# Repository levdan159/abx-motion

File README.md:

# ABX-Motion Rev 1.2b — Ethernet routing draft

Open [abx-motion.kicad_pro](abx-motion.kicad_pro) in the project root. The root PCB and schematic hierarchy now contain the reviewed Ethernet development checkpoint, promoted from [ABX-Motion-ETH](variants/ABX-Motion-ETH/README.txt). Assembly option: **ABX-MOTION-ETH**. No PoE.

Current [DRC cleanup verification](validation/drc-cleanup-20261024/README.txt): **0 DRC violations, 0 defined-net opens, 0 schematic-parity issues and 0 ERC violations**. No rules were relaxed or findings excluded. The 49 unwired Ethernet placement reserves are explicitly board-only and still excluded from BOM/CPL. A clean DRC does not make those reserves functional.

The dedicated Ethernet 3.3 V converter is schematic-integrated and routed, and connections displaced by Ethernet placement are restored. The W5500, RJ45, clock, protection, reset and SPI interface still have **49 unintegrated draft footprints**. This is **not a manufacturing release**. Zero opens on defined nets does not establish complete Ethernet connectivity.

The checkpoint retains the three onboard DRV8462 drivers, external stepper interfaces, eight-socket digital I/O bank, axis legends and thermal copper/TIM windows. The PCB is four layers; In1.Cu remains the ground plane. The audited project minimum clearance and track width are both 0.15 mm.

See [root promotion QA](validation/root-ethernet-promotion-20261024/README.txt), [Ethernet routing preview](variants/ABX-Motion-ETH/layout-review/routing-overview.png), and [remaining circuit requirements](variants/ABX-Motion-ETH/layout-review/power-routing-plan.txt). The earlier Rev1.2a CAD is recoverable from Git commit `ce34a43`; its [JLCPCB prototype package](production/rev-1.2a-20261023/README.txt) is preserved and **does not describe this Rev1.2b draft**. Earlier exports and renders remain historical. Do not run legacy rebuild/router scripts over the active root project.

The original local project settings were saved before promotion in `work/root-ethernet-promotion-20261024/before/`. Root schematic instance project names and library paths were adapted for `abx-motion`; the reviewed PCB was promoted, then obsolete copper, thermal-aperture routing and silkscreen were cleaned up with connectivity checks. Ethernet 3D models are bundled under `abx-3dmodels/ethernet/`; see the [model-loading verification](validation/root-model-fix-20261024/README.txt).

## Historical Rev 1.1 documentation

The content below describes the preserved Rev 1.1 prototype and its exports. StepStick socket details, firmware allocations, component counts and images below do not describe the active Rev 1.2b draft. The preserved Rev 1.1d manufacturing package is `production/rev-1.1d-20261020/`. Do not run legacy rebuild/router scripts over the active root placement.

# ABX-Motion Rev 1.1c prototype controller

Compact **157 × 105 mm, four-layer** ESP32-S3 motion controller. This layout is
intended for controlled prototype testing. Printed voltage, motor-power and
fuse ratings are design targets, not measured board ratings.

## Hardware

- ESP32-S3-WROOM-1-N8R2, native USB-C programming, RESET/BOOT buttons,
  CAN, RS-485, I²C OLED header and BACK/OK/FWD controls.
- Two DRV8701E brushed-motor bridges with encoder inputs, 10 mΩ shunts
  and configurable gate-drive resistors.
- Two StepStick sockets and external STEP/DIR/EN connectors. Check each
  carrier's pinout, enable polarity, voltage range and mode straps before use.
- Two SPDT relays. Contact ratings do not establish PCB current capability.
- XT60 input, Keystone 3557-2 fuse holder, reverse-polarity P-MOSFET,
  TVS3300 precision pulse clamp, 5 V buck and 3.3 V LDO.
- Front and rear exposed-copper gears (`F.Cu`/`F.Mask` and `B.Cu`/`B.Mask`)
  with white silkscreen text (`AUTOBOTIX` / `ABX-Motion Rev 1.1c`). Select ENIG for
  gold artwork.

## Compact I/O

J601–J606 use identical three-pin JST-PH headers. Read the per-pin markings:
output headers have a different function from limit headers.

| Headers | Channel | Pin 1 | Pin 2 | Pin 3 |
| --- | --- | --- | --- | --- |
| J601 | DC motor 1 limits | MIN | GND | MAX |
| J602 | DC motor 2 limits | MIN | GND | MAX |
| J603 | Stepper 1 limits | MIN | GND | MAX |
| J604 | Stepper 2 limits | MIN | GND | MAX |
| J605 | Auxiliary output 1 | +5V_OUT | GND | SW1 |
| J606 | Auxiliary output 2 | +5V_OUT | GND | SW2 |

The eight limit channels have 3.3 V pull-ups, series resistors and RC filtering.
Use dry contacts to ground or compatible 3.3 V logic. **Do not connect 12/24 V
sensors directly.** Normally closed contacts let firmware treat a broken wire
as an active limit. Configured as outputs, these are resistor-limited logic
signals, not load drivers.

Connect a 5 V auxiliary load between +5V_OUT and SW1/SW2. SW pins are low-side
MOSFET drains. Both headers share F5: **Littelfuse 1206L050/15YR, C151162**,
500 mA hold at 20 °C, 15 V. The PTC is not a precise 500 mA current limiter;
temperature, trip delay and the total 5 V supply budget constrain usable loads.

## Firmware and stopping

PCA9555 U601 is at I²C address 0x20 on GPIO41 (SDA) / GPIO42 (SCL).
Its active-low interrupt uses GPIO36; BACK uses GPIO21.
Port 0 bits 0–7 are limits in the table's MIN/MAX order.
Port 1 bits 0/1 command auxiliary outputs, bits 2/3 command active-low
stepper enables, and bit 4 reads E-stop status. Bits 5–7 are grounded and
must remain inputs.

On startup, keep both ports as inputs, write Port 1 output latch **0x0C**
(outputs off, steppers disabled), then configure Port 1 with **0xF0**. Keep
Port 0 configuration **0xFF** for limit sensing. Read inputs to acknowledge
interrupts. An ESP32 reset does not reset the independently powered expander;
reinitialize it on every boot and test reboot behavior under load. No application
firmware is supplied in this repository yet.

The hardware E-stop net disables DC bridges and gates onboard/external
stepper enables. Relays and auxiliary outputs remain powered. Verify stop
behavior with each actual attached driver. Firmware must block travel into an
active limit while allowing controlled retreat; I²C limit sensing is not an
independent hardware overtravel interlock.

## Validation and first power-up

**Prototype status:** CAD checks pass for the saved prototype candidate.
Powered motor, thermal and fault qualification requires the first boards;
it is not a prerequisite for fabricating them. Confirm relay alignment with
the assembler before assembly: the supplier CAD conflicts with Omron's hole
drawing. Full-power operation and the return-energy/protection envelope
remain unqualified. The small D2 TVS is not a braking-energy sink, and
parallel TVS parts do not guarantee current sharing. See
`validation/robustness-final-20261020/review.txt` and the matched files in
`production/rev-1.1d-20261020/`. Supplier numbered-pad checks verify D2,
U601 and all six PH connector directions.

The supply target is conventional 7S lithium ion (29.4 V fully charged), with
a 32 V normal ceiling. First power at the intended voltage needs controlled
fault energy/current, motors disconnected and drivers disabled. A 12 V test
is not required. Check rails, USB programming, expander defaults, all eight
inputs, auxiliary outputs and E-stop before adding one unloaded motor at low
current. Measure switching transients, rail ripple, current accuracy and
temperatures before increasing load. D2 is now TI TVS3300DRVR (C2863624):
33 V standoff, 40 V maximum clamp under TI's specified 8/20 us surge conditions.
The SON package rating is 35 A at 8/20 us but only 3.5 A at 10/1000 us. It is
not a continuous braking load. Regenerative loads require a battery/BMS that
accepts their charging current or a separately sized braking clamp. Do not
substitute a TMC2209 carrier for 7S/32 V use; its operating maximum is 29 V.
Q1 heating, LDO dissipation and motor-capacitor ripple capability also need
measurement. Confirm the OLED module's physical hole/header dimensions before
ordering (`H5`/`H6` M2 holes are at `23.30 mm` actual X spacing vs `23.0 mm`
nominal silkscreen callout, `23.80 mm` below `J208`); SSD1306 module names do
not guarantee a common hole pattern.

Assembly BOM correction (20 October 2026): StepStick sockets use four C27438
1x8 female strips, with 1.0 mm PCB holes per the supplier drawing. The earlier
C145755 entry was a temperature sensor and must not be assembled. The current
BOM has 66 supplier/footprint groups for 239 placements; repeated connector,
LED and switch selections are consolidated. Upload the matching new Gerbers,
BOM and CPL together. F1 is a holder; obtain the actual blade fuse separately.

Robustness revision (20 October 2026): R2=150k above R3=10k gives a nominal
**VBAT/16** ADC input. R313/R413=1k form 1:2 dividers with R304/R404; the MCU
now measures **SO/2**. Firmware must calculate shunt current using
`I = (2*Vadc - calibrated_SO_offset) / (20*0.010)` with actual gain/offset
calibration. Rev 1.1c separately lowers the chopping threshold through
R302/R402; the ADC divider does not set that threshold. R6=22k reduces battery
LED heating. All pre-existing signal routing and component positions except
D2's local footprint remain preserved. No application firmware is supplied.
Use the saved native design and the matching package. Legacy stage/router
scripts restore older checkpoints and must not be used to export this revision.

## Hardware revision

The current hardware identifier is **ABX-Motion Rev 1.1d**. `Rev` identifies
the PCB hardware; firmware versions are separate. Rev 1.1b included the
ADC input dividers, battery-divider/LED resistor updates, corrected socket
selection and assembly audit. Relay alignment needs assembler confirmation;
powered qualification follows prototype receipt. Revision lettering does
not imply qualified operating ratings. Rev 1.1c additionally changes R302/R402 from 30k to 12k (C22790) to lower
the DC current-chopping target from 14.75 A to 9.35 A nominal. The analytical
static corner estimate is about 6.7–11.8 A, before temperature drift, ground-layout errors and blanking/propagation
overshoot; it is not a guaranteed current bound. Layout and copper routing are unchanged. This may restrict torque
for low-voltage motors operated through PWM; it is not a 150 W power limiter.

## Motor robustness and bench acceptance

Design case: two DC motors, each drawing up to 150 W electrically for one
second; 300 W combined excludes StepStick loads and other peripherals. This
is a proposed intermittent operating envelope, not a measured board rating.
Motor winding current can exceed battery current under PWM. Current chopping
does not protect arbitrary low-inductance motors, brake-mode currents or a
sustained short. DRV8701 retries faults automatically; its die-temperature
shutdown does not measure the external MOSFETs or Q1.

Follow `validation/robustness-final-20261020/bench-procedure.txt` at the intended
pack voltage with fault energy limited before connecting motors. No physical
load, thermal, stall or regenerative test has yet been performed. Do not infer
safety from the 25 A holder label or 150 W motor power. Use actual phase-current
measurements, a timed stop and a verified return-energy path during testing.

## Thermal layout revision — Rev 1.1d

Local net-specific thermal vias and backside copper spread heat from Q1
and the motor bridge MOSFETs. A grounded top copper spreader connects the
ESP32 module centre pad to its surroundings, retaining its twelve existing
plated thermal holes and antenna keepout. U2 gains a small grounded spreader;
its SOT-23 package still limits continuous dissipation. Existing buck and
gate-driver thermal arrays remain unchanged. No component positions, lead
pads, original routing, electrical values or connector orientations change.
See `validation/thermal-20261020/review.txt` for checked scope and limitations.
MOSFET drain copper is electrically live; a common metal heatsink requires
an electrically insulating thermal interface. Added vias are outside solder
lands and tented on both faces. This is a heat-path improvement, not a
measured temperature or continuous-current qualification.

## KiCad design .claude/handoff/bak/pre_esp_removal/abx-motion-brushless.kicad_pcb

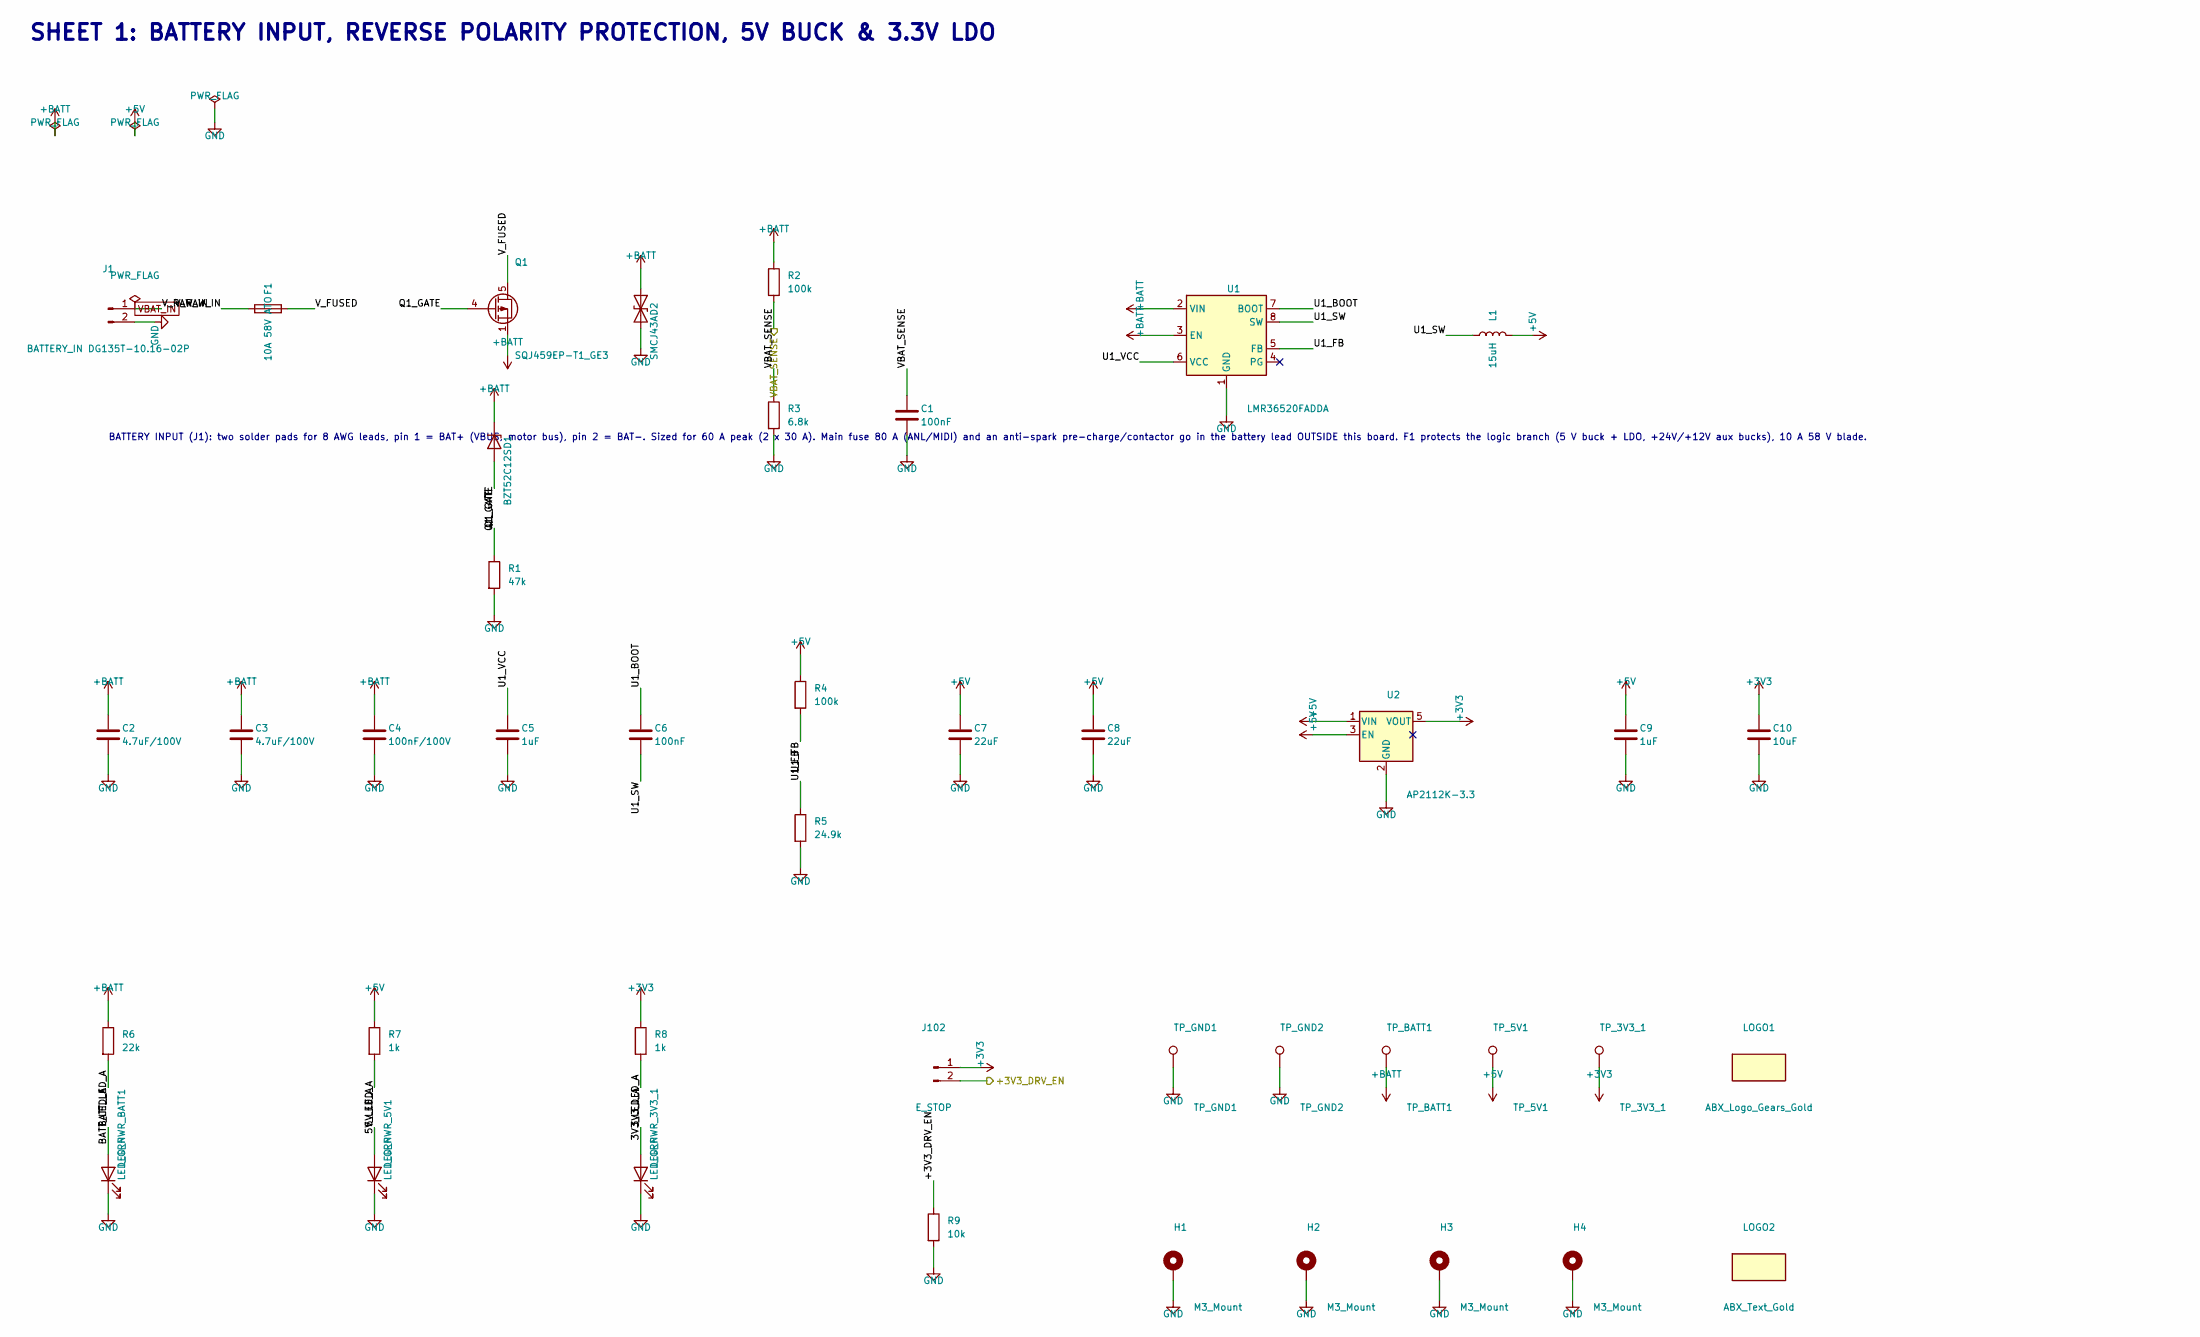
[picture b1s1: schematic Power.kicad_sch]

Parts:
C1, C6: 100nF; C_0603_1608Metric
C2, C3: 4.7uF/100V; C_1206_3216Metric
C4: 100nF/100V; C_0603_1608Metric
C5, C9: 1uF; C_0603_1608Metric
C7, C8: 22uF; C_1206_3216Metric
C10: 10uF; C_0805_2012Metric
D1: BZT52C12S; D_SOD-323
D2: SMCJ43A; D_SMC
F1: 10A 58V ATO; Fuseholder_Keystone_3557-2
H1, H2, H3, H4: M3_Mount; MountingHole_3.2mm_M3_Pad_Via
J1: BATTERY_IN DG135T-10.16-02P; ABX_Degson_DG135T-10.16-02P
J102: E_STOP; TerminalBlock_Phoenix_MKDS-1,5-2-5.08_1x02_P5.08mm_Horizont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
L1: 15uH; L_Bourns_SRP7028A_7.3x6.6mm
LED_PWR_3V3_1, LED_PWR_5V1: LED_GRN; LED_0603_1608Metric
LED_PWR_BATT1: LED_GRN; LED_0603_1608Metric
LOGO1: ABX_Logo_Gears_Gold
LOGO2: ABX_Text_Gold
Q1: SQJ459EP-T1_GE3; TDSON-8-1
R1: 47k; R_0603_1608Metric
R2, R4: 100k; R_0603_1608Metric
R3: 6.8k; R_0603_1608Metric
R5: 24.9k; R_0603_1608Metric
R6: 22k; R_0603_1608Metric
R7, R8: 1k; R_0603_1608Metric
R9: 10k; R_0603_1608Metric
TP_3V3_1: TP_3V3_1; TestPoint_Pad_D1.5mm
TP_5V1: TP_5V1; TestPoint_Pad_D1.5mm
TP_BATT1: TP_BATT1; TestPoint_Pad_D1.5mm
TP_GND1: TP_GND1; TestPoint_Pad_D1.5mm
TP_GND2: TP_GND2; TestPoint_Pad_D1.5mm
U1: LMR36520FADDA; Texas_HSOP-8-1EP_3.9x4.9mm_P1.27mm_ThermalVias
U2: AP2112K-3.3; SOT-23-5

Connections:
+3V3: C10.1, J102.1, R8.1, TP_3V3_1.1 (1_1), U2.5 (VOUT); also elsewhere on the board
+5V: C7.1, C8.1, C9.1, L1.2, R4.1, R7.1, TP_5V1.1 (1_1), U2.1 (VIN), U2.3 (EN); also elsewhere on the board
+BATT: C2.1, C3.1, C4.1, D1.1 (K), D2.1 (A1), Q1.1 (S), Q1.2 (S), Q1.3 (S), R2.1, R6.1, TP_BATT1.1 (1_1), U1.2 (VIN), U1.3 (EN); also elsewhere on the board
/+3V3_DRV_EN: J102.2, R9.1; also elsewhere on the board
/Power_Supply/3V3_LED_A: LED_PWR_3V3_1.2 (A), R8.2
/Power_Supply/5V_LED_A: LED_PWR_5V1.2 (A), R7.2
/Power_Supply/BATT_LED_A: LED_PWR_BATT1.2 (A), R6.2
/Power_Supply/Q1_GATE: D1.2 (A), Q1.4 (G), R1.1
/Power_Supply/U1_BOOT: C6.1, U1.7 (BOOT)
/Power_Supply/U1_FB: R4.2, R5.1, U1.5 (FB)
/Power_Supply/U1_SW: C6.2, L1.1, U1.8 (SW)
/Power_Supply/U1_VCC: C5.1, U1.6 (VCC)
/Power_Supply/V_FUSED: F1.2, Q1.5 (D)
/VBAT_SENSE: C1.1, R2.2, R3.1; also elsewhere on the board
VBAT_IN: F1.1, J1.1; also elsewhere on the board

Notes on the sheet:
SHEET 1: BATTERY INPUT, REVERSE POLARITY PROTECTION, 5V BUCK & 3.3V LDO
BATTERY INPUT (J1): two solder pads for 8 AWG leads, pin 1 = BAT+ (VBUS, motor bus), pin 2 = BAT-. Sized for 60 A peak (2 x 30 A). Main fuse 80 A (ANL/MIDI) and an anti-spark pre-charge/contactor go in the battery lead OUTSIDE this board. F1 protects the logic branch (5 V buck + LDO, +24V/+12V aux 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

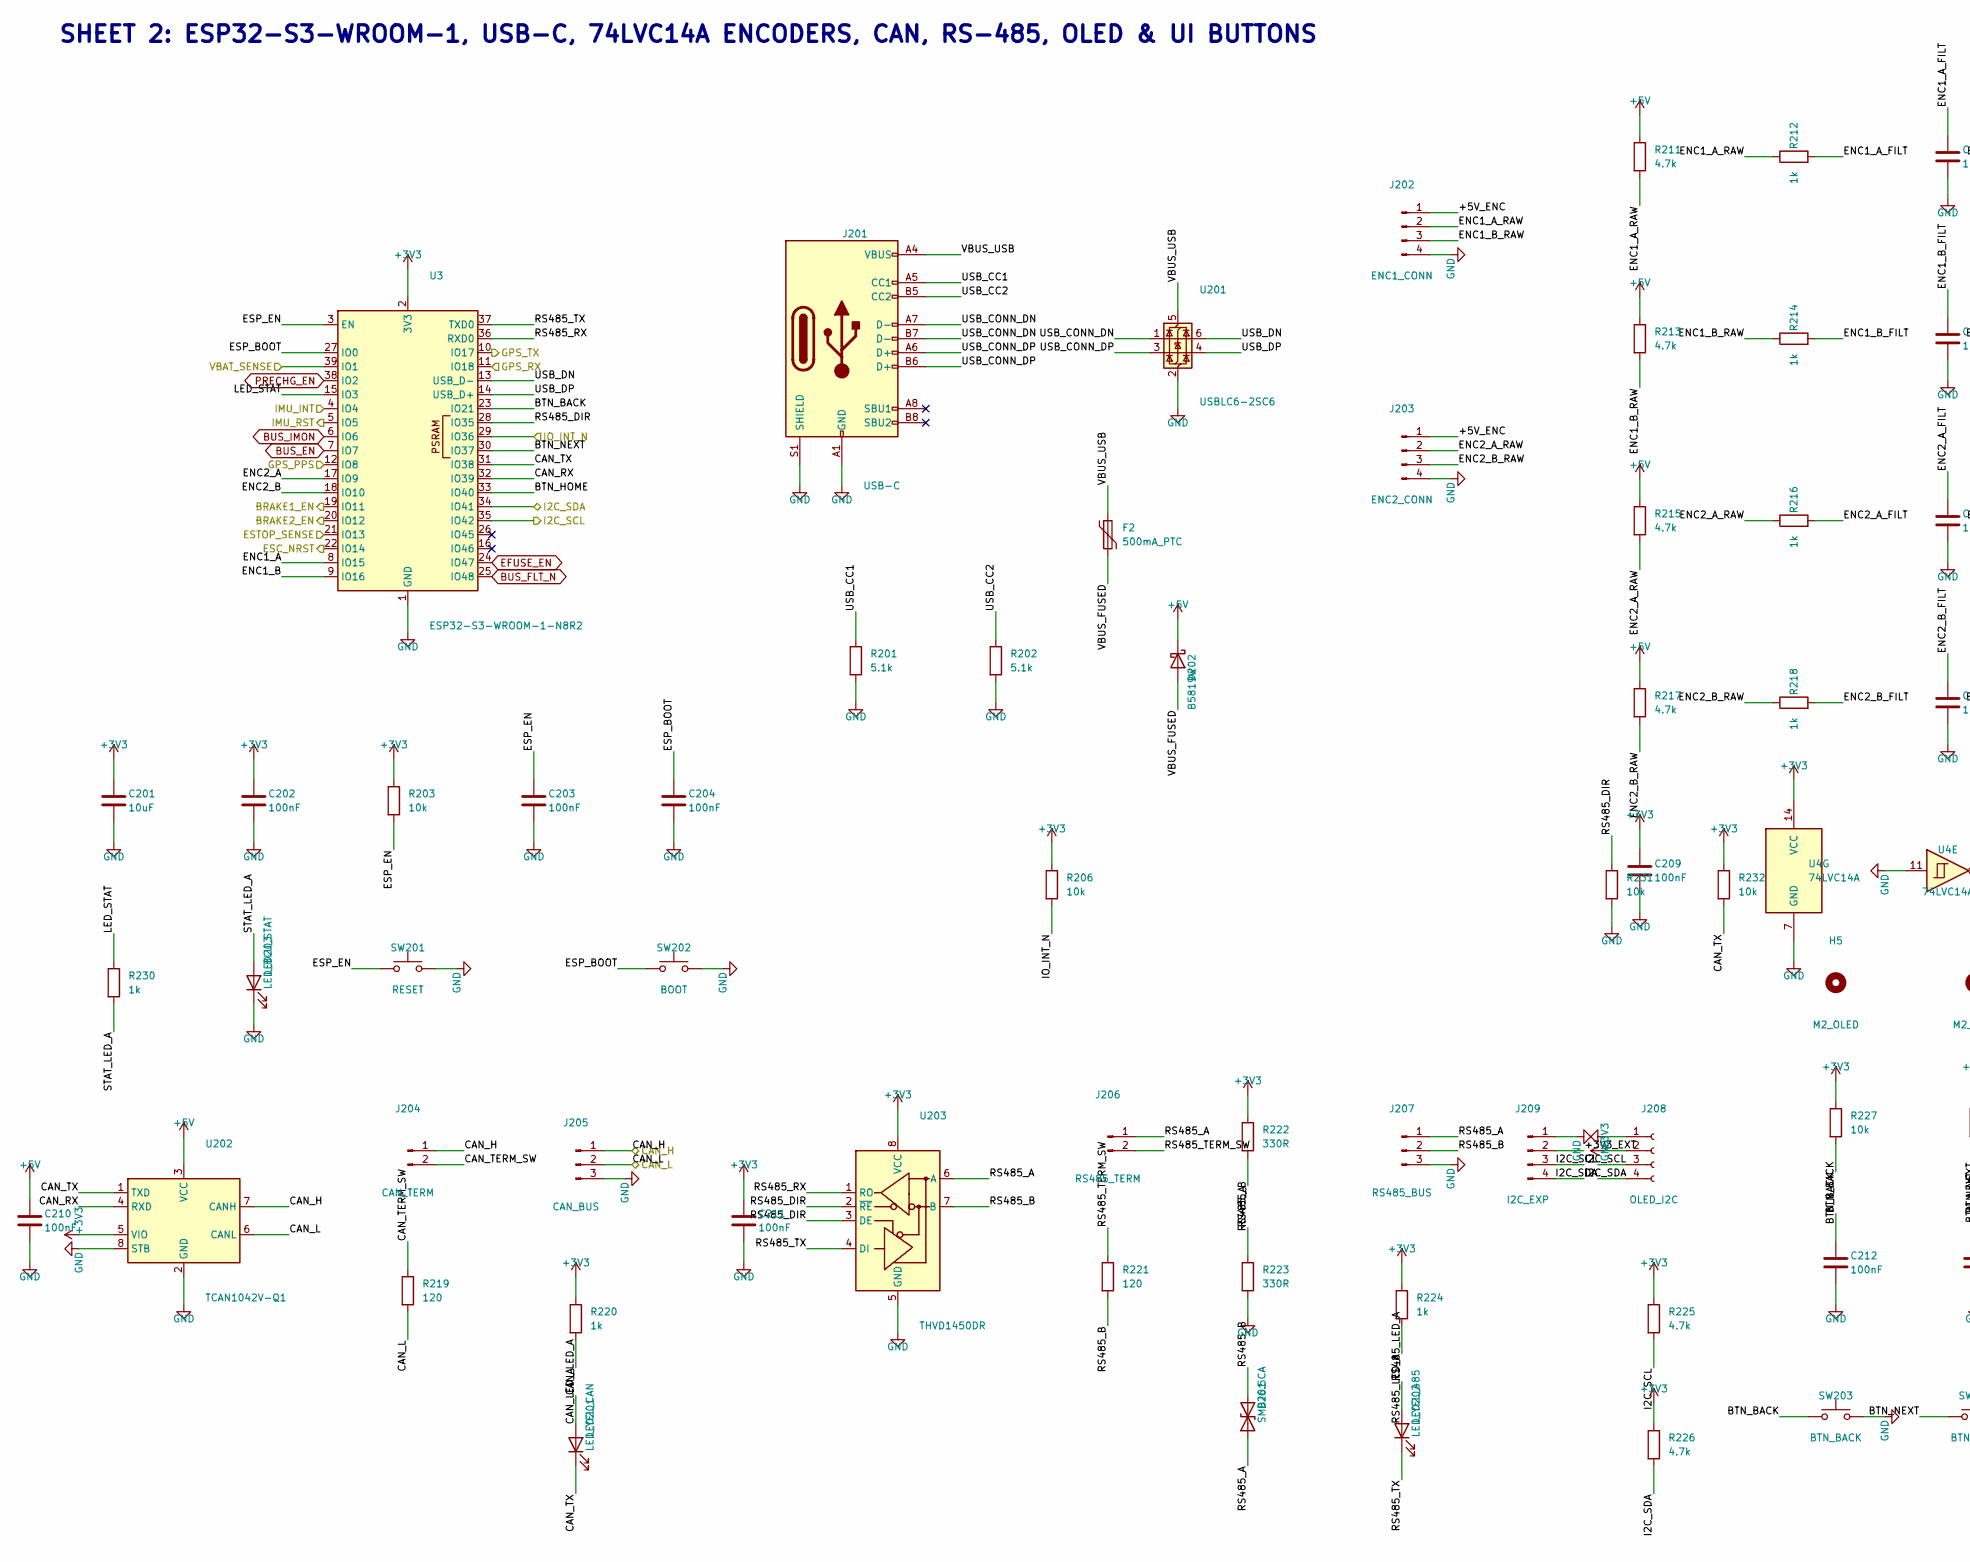
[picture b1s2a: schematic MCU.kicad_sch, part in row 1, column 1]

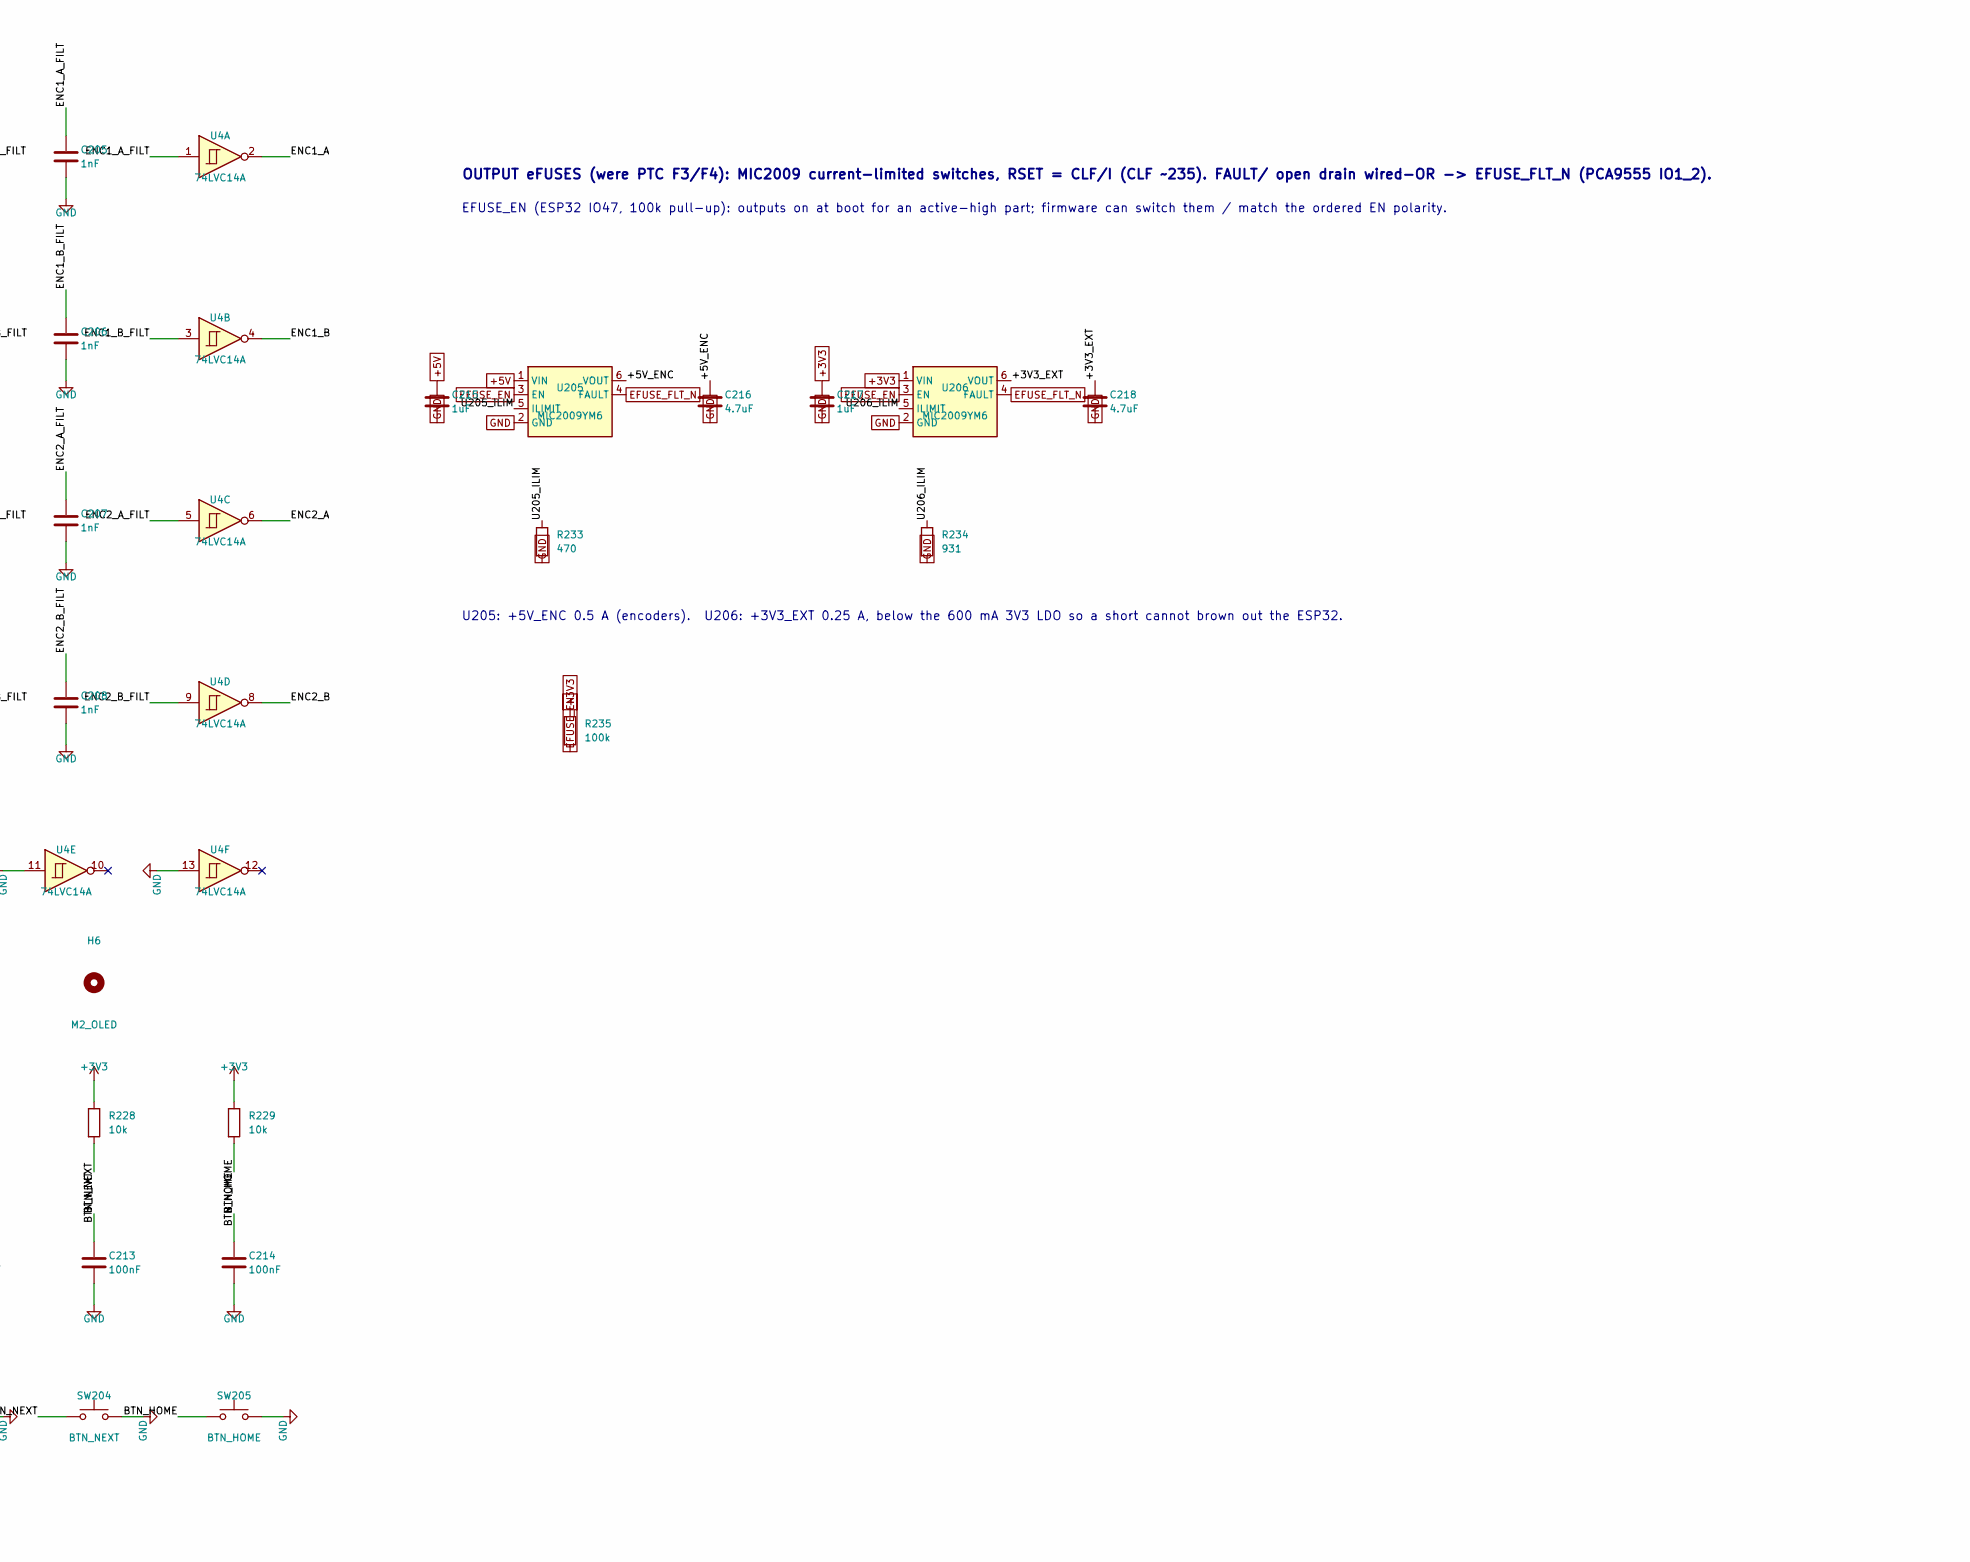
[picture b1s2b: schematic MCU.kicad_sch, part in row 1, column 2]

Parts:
C201: 10uF; C_0805_2012Metric
C202, C203, C204, C209, C210, C211, C212, C213, C214: 100nF; C_0603_1608Metric
C205, C206, C207, C208: 1nF; C_0603_1608Metric
C215, C217: 1uF; C_0603_1608Metric
C216, C218: 4.7uF; C_0805_2012Metric
D201: SMBJ6.5CA; D_SMB
D202: B5819W; D_SOD-123
F2: 500mA_PTC; Fuse_1206_3216Metric
H5, H6: M2_OLED; MountingHole_2.2mm_M2
J201: USB-C; USB_C_Receptacle_HRO_TYPE-C-31-M-12
J202: ENC1_CONN; JST_XH_B4B-XH-A_1x04_P2.50mm_Vertical
J203: ENC2_CONN; JST_XH_B4B-XH-A_1x04_P2.50mm_Vertical
J204: CAN_TERM; PinHeader_1x02_P2.54mm_Vertical
J205: CAN_BUS; TerminalBlock_Phoenix_MKDS-1,5-3-5.08_1x03_P5.08mm_Horizont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
J206: RS485_TERM; PinHeader_1x02_P2.54mm_Vertical
J207: RS485_BUS; TerminalBlock_Phoenix_MKDS-1,5-3-5.08_1x03_P5.08mm_Horizont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
J208: OLED_I2C; PinSocket_1x04_P2.54mm_Vertical
J209: I2C_EXP; JST_XH_B4B-XH-A_1x04_P2.50mm_Vertical
LED201: LED_YEL_CAN; LED_0603_1608Metric
LED202: LED_YEL_485; LED_0603_1608Metric
LED203: LED_BLU_STAT; LED_0603_1608Metric
R201, R202: 5.1k; R_0603_1608Metric
R203, R206, R227, R228, R229, R231, R232: 10k; R_0603_1608Metric
R211, R213, R215, R217, R225, R226: 4.7k; R_0603_1608Metric
R212, R214, R216, R218, R220, R224, R230: 1k; R_0603_1608Metric
R219, R221: 120; R_0603_1608Metric
R222, R223: 330R; R_0603_1608Metric
R233: 470; R_0603_1608Metric
R234: 931; R_0603_1608Metric
R235: 100k; R_0603_1608Metric
SW201: RESET; SW_SPST_B3U-1000P
SW202: BOOT; SW_SPST_B3U-1000P
SW203: BTN_BACK; SW_SPST_B3U-1000P
SW204: BTN_NEXT; SW_SPST_B3U-1000P
SW205: BTN_HOME; SW_SPST_B3U-1000P
U3: ESP32-S3-WROOM-1-N8R2; ESP32-S3-WROOM-1
U4: 74LVC14A; SOIC-14_3.9x8.7mm_P1.27mm
U201: USBLC6-2SC6; SOT-23-6
U202: TCAN1042V-Q1; SOIC-8_3.9x4.9mm_P1.27mm
U203: THVD1450DR; SOIC-8_3.9x4.9mm_P1.27mm
U205, U206: MIC2009YM6; SOT-23-6

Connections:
+3V3: C201.1, C202.1, C209.1, C211.1, C217.1, J208.2, R203.1, R206.1, R220.1, R222.1, R224.1, R225.1, R226.1, R227.1, R228.1, R229.1, R232.1, R235.1, U3.2 (3V3), U4.14 (VCC), U202.5 (VIO), U203.8 (VCC), U206.1 (VIN); also elsewhere on the board
+5V: C210.1, C215.1, D202.1 (K), R211.1, R213.1, R215.1, R217.1, U202.3 (VCC), U205.1 (VIN); also elsewhere on the board
/BRAKE1_EN: U3.19 (IO11); also elsewhere on the board
/BRAKE2_EN: U3.20 (IO12); also elsewhere on the board
/CAN_H: J204.1, J205.1, U202.7 (CANH); also elsewhere on the board
/CAN_L: J205.2, R219.2, U202.6 (CANL); also elsewhere on the board
/ESC_NRST: U3.22 (IO14); also elsewhere on the board
/ESTOP_SENSE: U3.21 (IO13); also elsewhere on the board
/GPS_PPS: U3.12 (IO8); also elsewhere on the board
/GPS_RX: U3.11 (IO18); also elsewhere on the board
/GPS_TX: U3.10 (IO17); also elsewhere on the board
/I2C_SCL: J208.3, J209.3, R225.2, U3.35 (IO42); also elsewhere on the board
/I2C_SDA: J208.4, J209.4, R226.2, U3.34 (IO41); also elsewhere on the board
/IMU_INT: U3.4 (IO4); also elsewhere on the board
/IMU_RST: U3.5 (IO5); also elsewhere on the board
/IO_INT_N: R206.2, U3.29 (IO36); also elsewhere on the board
/MCU_and_Encoders/+3V3_EXT: C218.1, J209.2, U206.6 (VOUT)
/MCU_and_Encoders/+5V_ENC: C216.1, J202.1, J203.1, U205.6 (VOUT)
/MCU_and_Encoders/BTN_BACK: C212.1, R227.2, SW203.1, U3.23 (IO21)
/MCU_and_Encoders/BTN_HOME: C214.1, R229.2, SW205.1, U3.33 (IO40)
/MCU_and_Encoders/BTN_NEXT: C213.1, R228.2, SW204.1, U3.30 (IO37)
/MCU_and_Encoders/CAN_LED_A: LED201.2 (A), R220.2
/MCU_and_Encoders/CAN_RX: U3.32 (IO39), U202.4 (RXD)
/MCU_and_Encoders/CAN_TERM_SW: J204.2, R219.1
/MCU_and_Encoders/CAN_TX: LED201.1 (K), R232.2, U3.31 (IO38), U202.1 (TXD)
/MCU_and_Encoders/ENC1_A: U3.8 (IO15), U4.2
/MCU_and_Encoders/ENC1_A_FILT: C205.1, R212.2, U4.1
/MCU_and_Encoders/ENC1_A_RAW: J202.2, R211.2, R212.1
/MCU_and_Encoders/ENC1_B: U3.9 (IO16), U4.4
/MCU_and_Encoders/ENC1_B_FILT: C206.1, R214.2, U4.3
/MCU_and_Encoders/ENC1_B_RAW: J202.3, R213.2, R214.1
/MCU_and_Encoders/ENC2_A: U3.17 (IO9), U4.6
/MCU_and_Encoders/ENC2_A_FILT: C207.1, R216.2, U4.5
/MCU_and_Encoders/ENC2_A_RAW: J203.2, R215.2, R216.1
/MCU_and_Encoders/ENC2_B: U3.18 (IO10), U4.8
/MCU_and_Encoders/ENC2_B_FILT: C208.1, R218.2, U4.9
/MCU_and_Encoders/ENC2_B_RAW: J203.3, R217.2, R218.1
/MCU_and_Encoders/ESP_BOOT: C204.1, SW202.1, U3.27 (IO0)
/MCU_and_Encoders/ESP_EN: C203.1, R203.2, SW201.1, U3.3 (EN)
/MCU_and_Encoders/LED_STAT: R230.1, U3.15 (IO3)
/MCU_and_Encoders/RS485_A: D201.1 (A1), J206.1, J207.1, R222.2, U203.6 (A)
/MCU_and_Encoders/RS485_B: D201.2 (A2), J207.2, R221.2, R223.1, U203.7 (B)
/MCU_and_Encoders/RS485_DIR: R231.1, U3.28 (IO35), U203.2 (~RE), U203.3 (DE)
/MCU_and_Encoders/RS485_LED_A: LED202.2 (A), R224.2
/MCU_and_Encoders/RS485_RX: U3.36 (RXD0), U203.1 (RO)
/MCU_and_Encoders/RS485_TERM_SW: J206.2, R221.1
/MCU_and_Encoders/RS485_TX: LED202.1 (K), U3.37 (TXD0), U203.4 (DI)
/MCU_and_Encoders/STAT_LED_A: LED203.2 (A), R230.2
/MCU_and_Encoders/U205_ILIM: R233.1, U205.5 (ILIMIT)
/MCU_and_Encoders/U206_ILIM: R234.1, U206.5 (ILIMIT)
/MCU_and_Encoders/USB_CC1: J201.A5 (CC1), R201.1
/MCU_and_Encoders/USB_CC2: J201.B5 (CC2), R202.1
/MCU_and_Encoders/USB_CONN_DN: J201.A7 (D-), J201.B7 (D-), U201.1 (I/O1)
/MCU_and_Encoders/USB_CONN_DP: J201.A6 (D+), J201.B6 (D+), U201.3 (I/O2)
/MCU_and_Encoders/USB_DN: U3.13 (USB_D-), U201.6 (I/O1)
/MCU_and_Encoders/USB_DP: U3.14 (USB_D+), U201.4 (I/O2)
/MCU_and_Encoders/VBUS_FUSED: D202.2 (A), F2.2
/MCU_and_Encoders/VBUS_USB: F2.1, J201.A4 (VBUS), J201.A9 (VBUS), J201.B4 (VBUS), J201.B9 (VBUS), U201.5 (VBUS)
/VBAT_SENSE: U3.39 (IO1); also elsewhere on the board
BUS_EN: U3.7 (IO7); also elsewhere on the board
BUS_FLT_N: U3.25 (IO48); also elsewhere on the board
BUS_IMON: U3.6 (IO6); also elsewhere on the board
EFUSE_EN: R235.2, U3.24 (IO47), U205.3 (EN), U206.3 (EN); also elsewhere on the board
EFUSE_FLT_N: U205.4 (FAULT), U206.4 (FAULT); also elsewhere on the board
PRECHG_EN: U3.38 (IO2); also elsewhere on the board

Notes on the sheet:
SHEET 2: ESP32-S3-WROOM-1, USB-C, 74LVC14A ENCODERS, CAN, RS-485, OLED & UI BUTTONS
OUTPUT eFUSES (were PTC F3/F4): MIC2009 current-limited switches, RSET = CLF/I (CLF ~235). FAULT/ open drain wired-OR -> EFUSE_FLT_N (PCA9555 IO1_2).
EFUSE_EN (ESP32 IO47, 100k pull-up): outputs on at boot for an active-high part; firmware can switch them / match the ordered EN polarity.
U205: +5V_ENC 0.5 A (encoders). U206: +3V3_EXT 0.25 A, below the 600 mA 3V3 LDO so a short cannot brown out the ESP32.

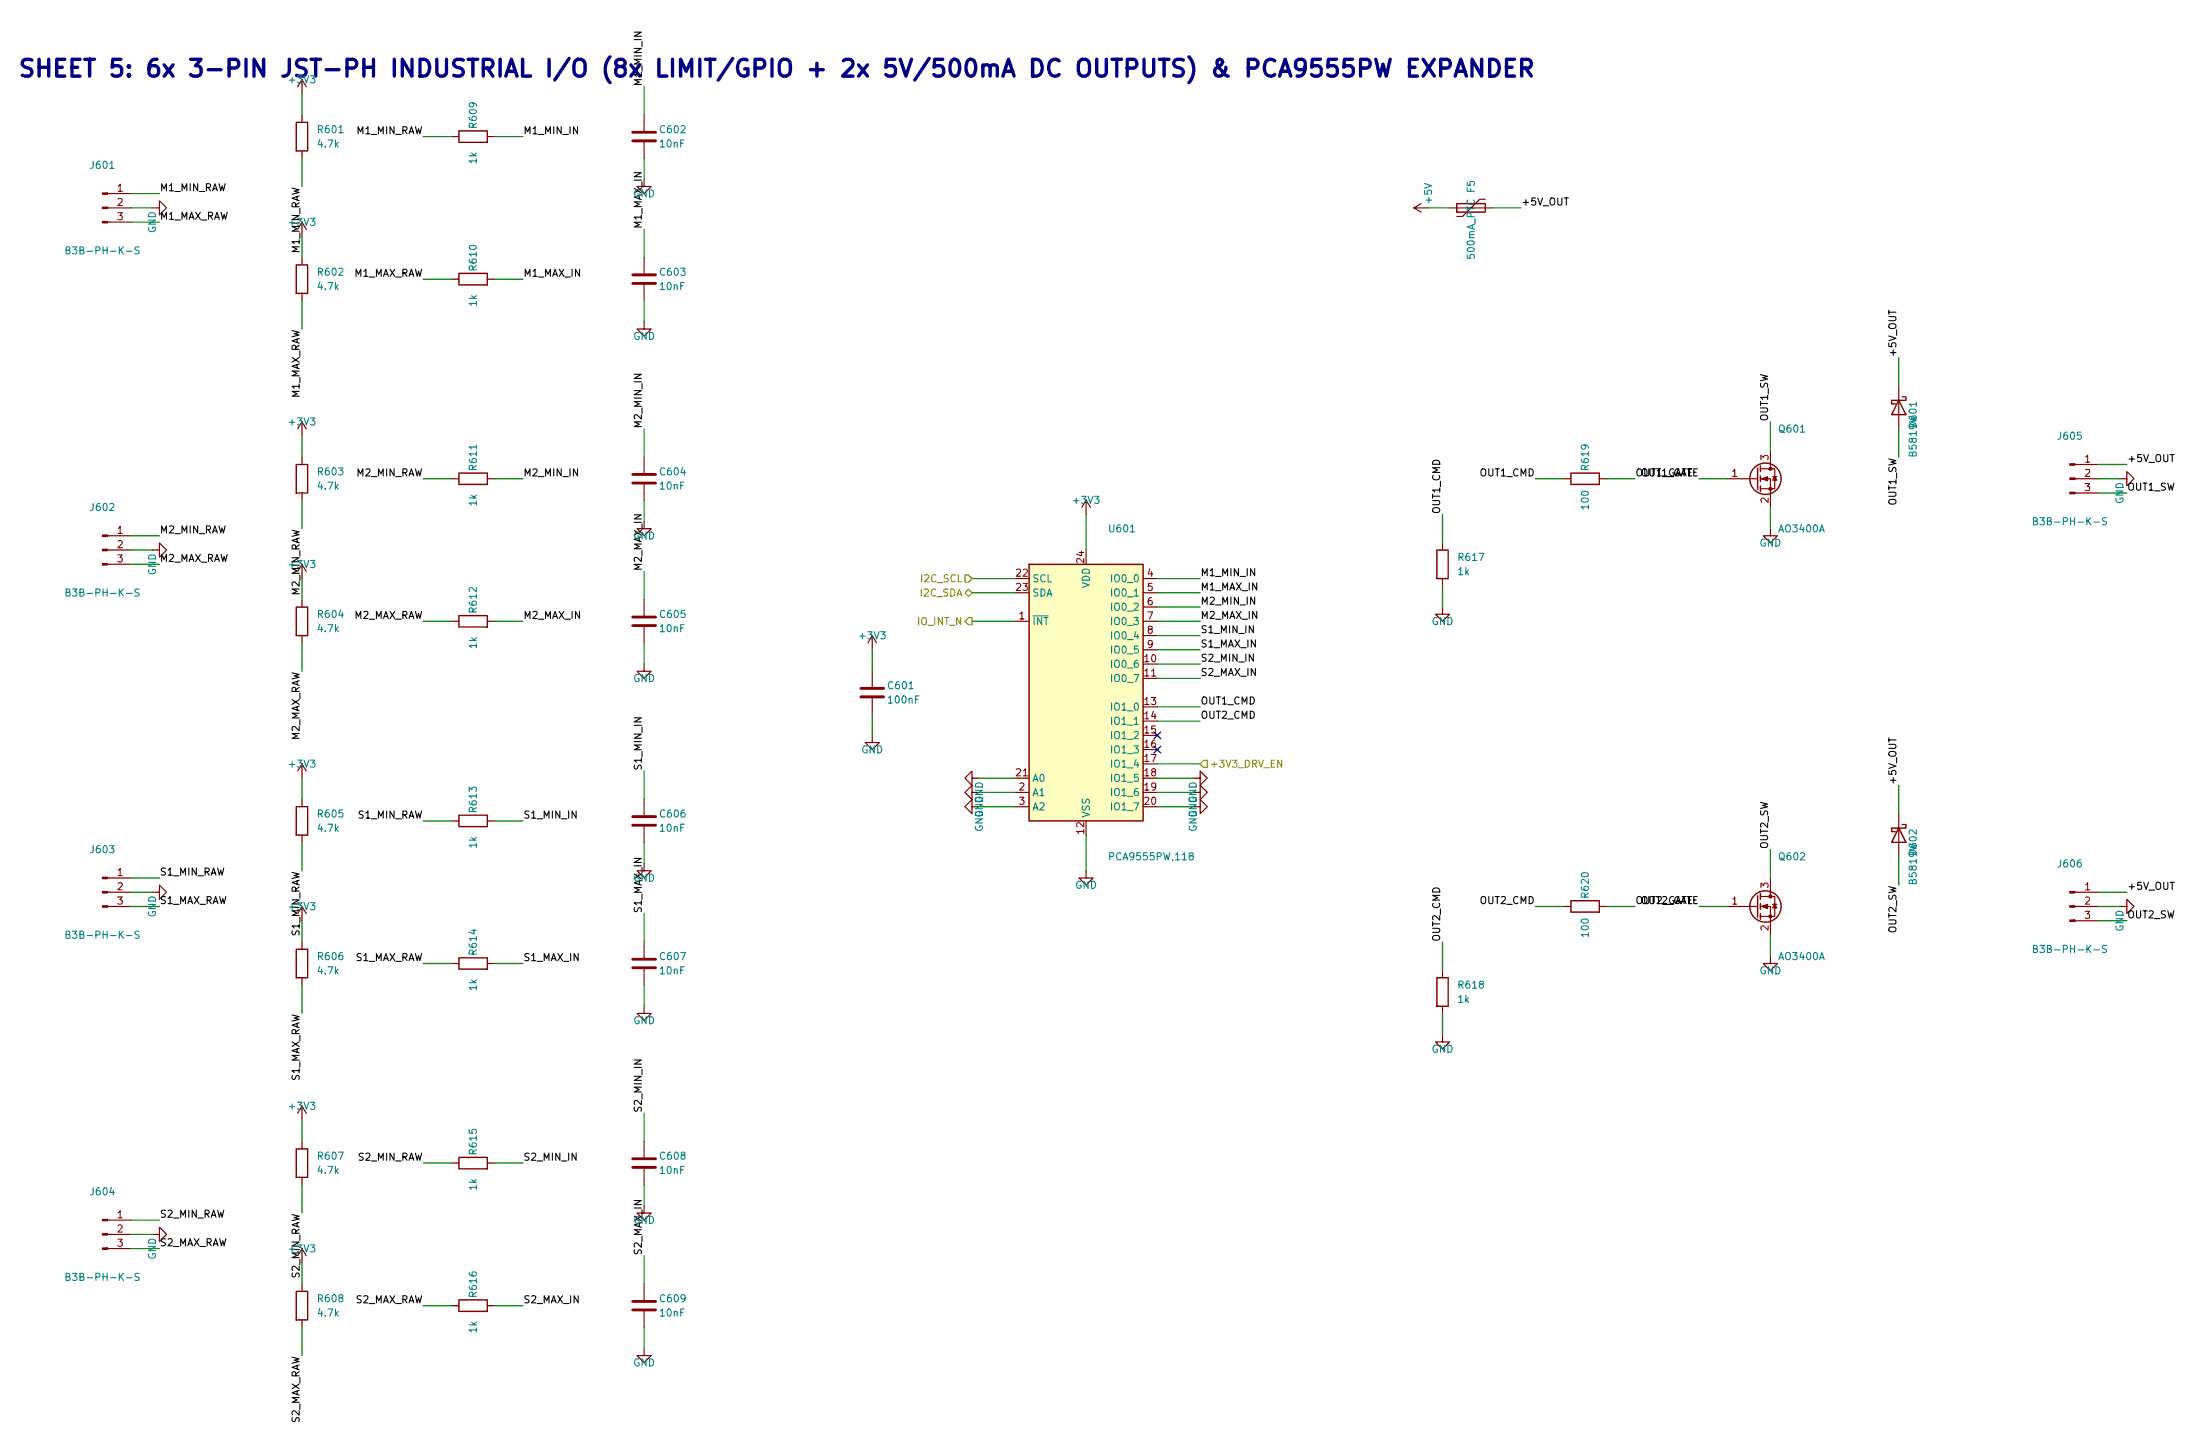
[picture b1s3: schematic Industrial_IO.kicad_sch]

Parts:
C601: 100nF; C_0603_1608Metric
C602, C603, C604, C605, C606, C607, C608, C609: 10nF; C_0603_1608Metric
D601, D602: B5819W; D_SOD-123
F5: 500mA_PTC; Fuse_1206_3216Metric
J601, J602, J603, J604, J605, J606: B3B-PH-K-S; JST_PH_B3B-PH-K_1x03_P2.00mm_Vertical
Q601, Q602: AO3400A; SOT-23
R601, R602, R603, R604, R605, R606, R607, R608: 4.7k; R_0603_1608Metric
R609, R610, R611, R612, R613, R614, R615, R616, R617, R618: 1k; R_0603_1608Metric
R619, R620: 100; R_0603_1608Metric
U601: PCA9555PW,118; TSSOP-24_4.4x7.8mm_P0.65mm

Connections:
+3V3: C601.1, R601.1, R602.1, R603.1, R604.1, R605.1, R606.1, R607.1, R608.1, U601.24 (VDD); also elsewhere on the board
/+3V3_DRV_EN: U601.17 (IO1_4); also elsewhere on the board
/I2C_SCL: U601.22 (SCL); also elsewhere on the board
/I2C_SDA: U601.23 (SDA); also elsewhere on the board
/IO_INT_N: U601.1 (~INT); also elsewhere on the board
/Industrial_IO/+5V_OUT: D601.1 (K), D602.1 (K), F5.2, J605.1, J606.1; also elsewhere on the board
/Industrial_IO/M1_MAX_IN: C603.1, R610.2, U601.5 (IO0_1)
/Industrial_IO/M1_MAX_RAW: J601.3, R602.2, R610.1
/Industrial_IO/M1_MIN_IN: C602.1, R609.2, U601.4 (IO0_0)
/Industrial_IO/M1_MIN_RAW: J601.1, R601.2, R609.1
/Industrial_IO/M2_MAX_IN: C605.1, R612.2, U601.7 (IO0_3)
/Industrial_IO/M2_MAX_RAW: J602.3, R604.2, R612.1
/Industrial_IO/M2_MIN_IN: C604.1, R611.2, U601.6 (IO0_2)
/Industrial_IO/M2_MIN_RAW: J602.1, R603.2, R611.1
/Industrial_IO/OUT1_CMD: R617.1, R619.1, U601.13 (IO1_0)
/Industrial_IO/OUT1_GATE: Q601.1 (G), R619.2
/Industrial_IO/OUT1_SW: D601.2 (A), J605.3, Q601.3 (D)
/Industrial_IO/OUT2_CMD: R618.1, R620.1, U601.14 (IO1_1)
/Industrial_IO/OUT2_GATE: Q602.1 (G), R620.2
/Industrial_IO/OUT2_SW: D602.2 (A), J606.3, Q602.3 (D)
/Industrial_IO/S1_MAX_IN: C607.1, R614.2, U601.9 (IO0_5)
/Industrial_IO/S1_MAX_RAW: J603.3, R606.2, R614.1
/Industrial_IO/S1_MIN_IN: C606.1, R613.2, U601.8 (IO0_4)
/Industrial_IO/S1_MIN_RAW: J603.1, R605.2, R613.1
/Industrial_IO/S2_MAX_IN: C609.1, R616.2, U601.11 (IO0_7)
/Industrial_IO/S2_MAX_RAW: J604.3, R608.2, R616.1
/Industrial_IO/S2_MIN_IN: C608.1, R615.2, U601.10 (IO0_6)
/Industrial_IO/S2_MIN_RAW: J604.1, R607.2, R615.1
BRK_FLT_N: U601.16 (IO1_3); also elsewhere on the board
EFUSE_FLT_N: U601.15 (IO1_2); also elsewhere on the board

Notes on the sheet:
SHEET 5: 6x 3-PIN JST-PH INDUSTRIAL I/O (8x LIMIT/GPIO + 2x 5V/500mA DC OUTPUTS) & PCA9555PW EXPANDER
